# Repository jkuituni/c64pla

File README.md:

# c64pla
Implementation of the SuperPLA in the c64 'c' version in VHDL done together with Frank Buss. Note, that this version does work only as the normal SuperPLA (chip number 251715), not the one with integrated color SRAM (chip number 252535).

This is a fork from the Frank Buss' repository as that is where the original work was done. For additional information check out the webpage about this project :

https://frank-buss.de/c64/pla/index.html

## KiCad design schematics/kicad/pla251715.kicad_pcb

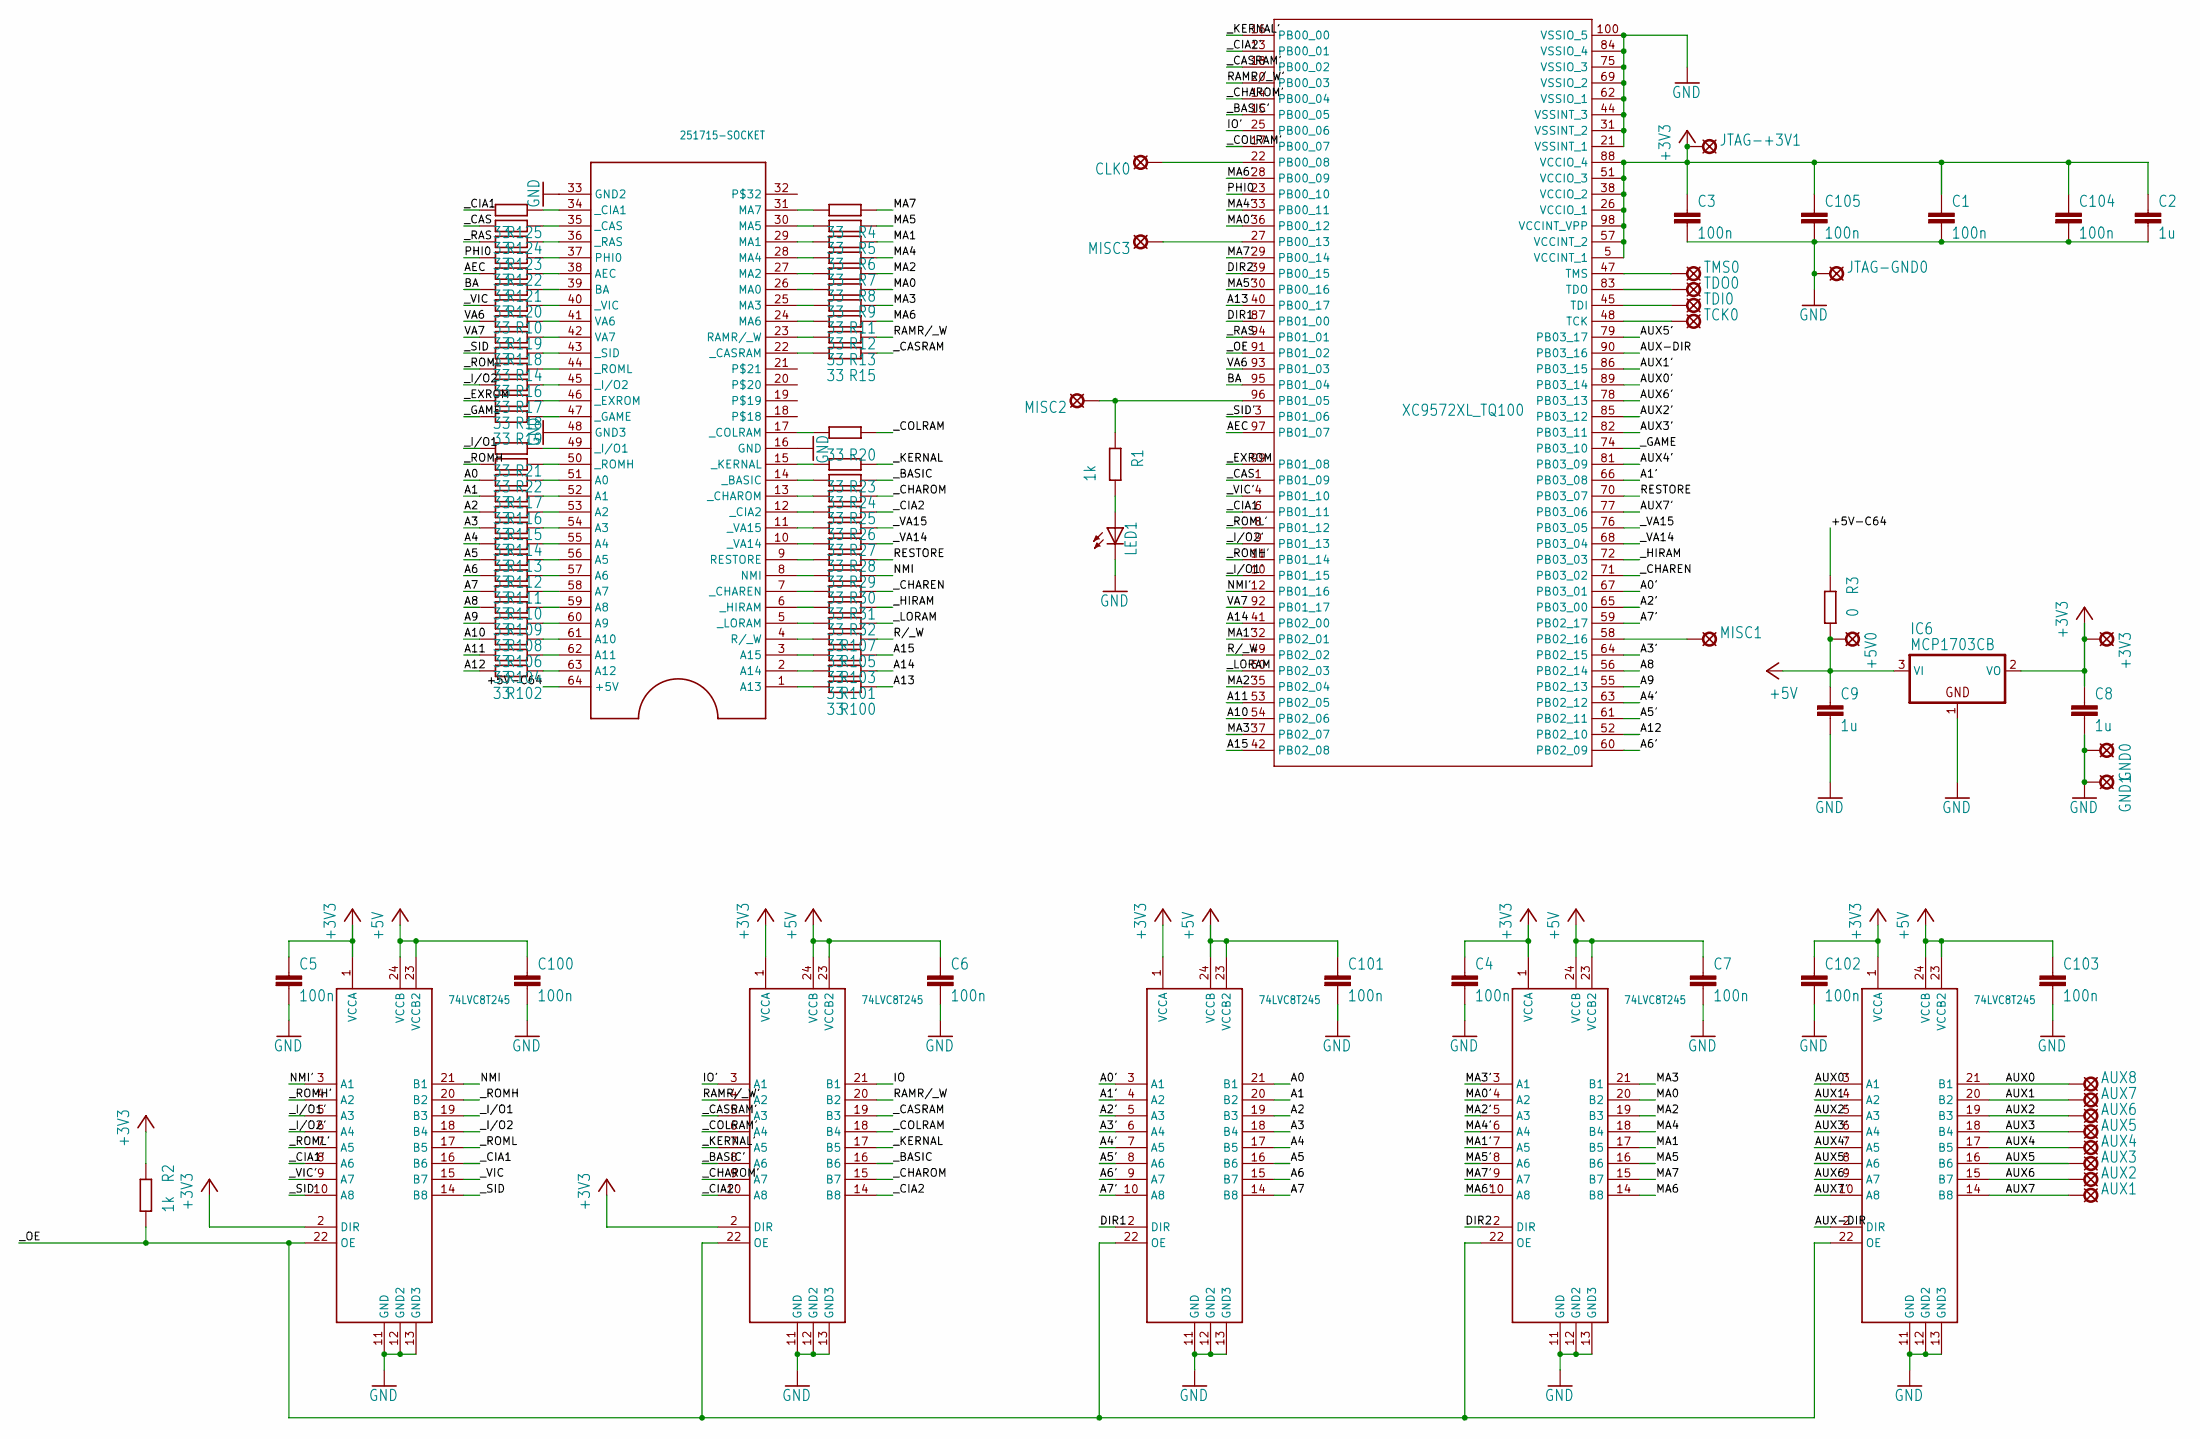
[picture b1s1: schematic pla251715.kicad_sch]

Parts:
+3V3, +5V0: LSP10
AUX1, AUX2, AUX3, AUX4, AUX5, AUX6, AUX7, AUX8: LSP10
C1, C3, C4, C5, C6, C7, C100, C101, C102, C103, C104, C105: 100n; C0603
C2, C8, C9: 1u; C1210
CLK0: LSP10
GND0, GND1: LSP10
IC1, IC3, IC4, IC5, IC100: 74LVC8T245; TSSOP24
IC2: XC9572XL_TQ100; TQ100
IC6: MCP1703CB; SOT23
JTAG-+3V1: LSP10
JTAG-GND0: LSP10
LED1: LED5MM
MISC1, MISC2, MISC3: LSP10
PLA-SOCKET0: 251715-SOCKET; 64-SPDIP
R1, R2: 1k; R0805
R3: 0; R0805
R4, R5, R6, R7, R8, R9, R10, R11, R12, R13, R14, R15, R16, R17, R18, R19, R20, R21, R22, R23, R24, R25, R26, R27, R28, R29, R30, R31, R32, R100, R101, R102, R103, R104, R105, R106, R107, R108, R109, R110, R111, R112, R113, R114, R115, R116, R117, R118, R119, R120, R121, R122, R123, R124, R125: 33; R0402
TCK0: LSP10
TDI0: LSP10
TDO0: LSP10
TMS0: LSP10

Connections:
+3V3: +3V3.MP, C1.1, C2.1, C3.1, C4.1, C5.1, C8.1, C102.1, C104.1, C105.1, IC1.1 (VCCA), IC2.5 (VCCINT_1), IC2.26 (VCCIO_1), IC2.38 (VCCIO_2), IC2.51 (VCCIO_3), IC2.57 (VCCINT_2), IC2.88 (VCCIO_4), IC2.98 (VCCINT_VPP), IC3.1 (VCCA), IC3.2 (DIR), IC4.1 (VCCA), IC4.2 (DIR), IC5.1 (VCCA), IC6.2 (VO), IC100.1 (VCCA), JTAG-+3V1.MP, R2.1
+5V: +5V0.MP, C6.1, C7.1, C9.1, C100.1, C101.1, C103.1, IC1.23 (VCCB2), IC1.24 (VCCB), IC3.23 (VCCB2), IC3.24 (VCCB), IC4.23 (VCCB2), IC4.24 (VCCB), IC5.23 (VCCB2), IC5.24 (VCCB), IC6.3 (VI), IC100.23 (VCCB2), IC100.24 (VCCB), R3.2
+5V-C64: PLA-SOCKET0.64 (+5V), R3.1
A0: IC100.21 (B1), R117.2
A0': IC2.67 (PB03_01), IC100.3 (A1)
A1: IC100.20 (B2), R116.2
A1': IC2.66 (PB03_08), IC100.4 (A2)
A2: IC100.19 (B3), R115.2
A2': IC2.65 (PB03_00), IC100.5 (A3)
A3: IC100.18 (B4), R114.2
A3': IC2.64 (PB02_15), IC100.6 (A4)
A4: IC100.17 (B5), R113.2
A4': IC2.63 (PB02_12), IC100.7 (A5)
A5: IC100.16 (B6), R112.2
A5': IC2.61 (PB02_11), IC100.8 (A6)
A6: IC100.15 (B7), R111.2
A6': IC2.60 (PB02_09), IC100.9 (A7)
A7: IC100.14 (B8), R110.2
A7': IC2.59 (PB02_17), IC100.10 (A8)
A8: IC2.56 (PB02_14), R109.2
A9: IC2.55 (PB02_13), R108.2
A10: IC2.54 (PB02_06), R106.2
A11: IC2.53 (PB02_05), R104.2
A12: IC2.52 (PB02_10), R102.2
A13: IC2.40 (PB00_17), R100.1
A14: IC2.41 (PB02_00), R101.1
A15: IC2.42 (PB02_08), R103.1
AEC: IC2.97 (PB01_07), R121.2
AUX0: AUX8.MP, IC1.21 (B1)
AUX0': IC1.3 (A1), IC2.89 (PB03_14)
AUX1: AUX7.MP, IC1.20 (B2)
AUX1': IC1.4 (A2), IC2.86 (PB03_15)
AUX2: AUX6.MP, IC1.19 (B3)
AUX2': IC1.5 (A3), IC2.85 (PB03_12)
AUX3: AUX5.MP, IC1.18 (B4)
AUX3': IC1.6 (A4), IC2.82 (PB03_11)
AUX4: AUX4.MP, IC1.17 (B5)
AUX4': IC1.7 (A5), IC2.81 (PB03_09)
AUX5: AUX3.MP, IC1.16 (B6)
AUX5': IC1.8 (A6), IC2.79 (PB03_17)
AUX6: AUX2.MP, IC1.15 (B7)
AUX6': IC1.9 (A7), IC2.78 (PB03_13)
AUX7: AUX1.MP, IC1.14 (B8)
AUX7': IC1.10 (A8), IC2.77 (PB03_06)
AUX-DIR: IC1.2 (DIR), IC2.90 (PB03_16)
BA: IC2.95 (PB01_04), R120.2
DIR1: IC2.87 (PB01_00), IC100.2 (DIR)
DIR2: IC2.39 (PB00_15), IC5.2 (DIR)
GND: C1.2, C2.2, C3.2, C4.2, C5.2, C6.2, C7.2, C8.2, C9.2, C100.2, C101.2, C102.2, C103.2, C104.2, C105.2, GND0.MP, GND1.MP, IC1.11 (GND), IC1.12 (GND2), IC1.13 (GND3), IC2.21 (VSSINT_1), IC2.31 (VSSINT_2), IC2.44 (VSSINT_3), IC2.62 (VSSIO_1), IC2.69 (VSSIO_2), IC2.75 (VSSIO_3), IC2.84 (VSSIO_4), IC2.100 (VSSIO_5), IC3.11 (GND), IC3.12 (GND2), IC3.13 (GND3), IC4.11 (GND), IC4.12 (GND2), IC4.13 (GND3), IC5.11 (GND), IC5.12 (GND2), IC5.13 (GND3), IC6.1 (GND), IC100.11 (GND), IC100.12 (GND2), IC100.13 (GND3), JTAG-GND0.MP, LED1.K (C), PLA-SOCKET0.16 (GND), PLA-SOCKET0.33 (GND2), PLA-SOCKET0.48 (GND3)
IO: IC4.21 (B1)
IO': IC2.25 (PB00_06), IC4.3 (A1)
MA0: IC5.20 (B2), R9.1
MA0': IC2.36 (PB00_12), IC5.4 (A2)
MA1: IC5.17 (B5), R6.1
MA1': IC2.32 (PB02_01), IC5.7 (A5)
MA2: IC5.19 (B3), R8.1
MA2': IC2.35 (PB02_04), IC5.5 (A3)
MA3: IC5.21 (B1), R11.1
MA3': IC2.37 (PB02_07), IC5.3 (A1)
MA4: IC5.18 (B4), R7.1
MA4': IC2.33 (PB00_11), IC5.6 (A4)
MA5: IC5.16 (B6), R5.1
MA5': IC2.30 (PB00_16), IC5.8 (A6)
MA6: IC5.14 (B8), R12.1
MA6': IC2.28 (PB00_09), IC5.10 (A8)
MA7: IC5.15 (B7), R4.1
MA7': IC2.29 (PB00_14), IC5.9 (A7)
unnamed: IC2.96 (PB01_05), MISC2.MP, R1.1
unnamed: IC2.58 (PB02_16), MISC1.MP
unnamed: IC2.27 (PB00_13), MISC3.MP
unnamed: LED1.A, R1.2
unnamed: CLK0.MP, IC2.22 (PB00_08)
unnamed: PLA-SOCKET0.17 (_COLRAM), R20.2
unnamed: PLA-SOCKET0.31 (MA7), R4.2
unnamed: PLA-SOCKET0.30 (MA5), R5.2
unnamed: PLA-SOCKET0.15 (_KERNAL), R23.2
unnamed: PLA-SOCKET0.29 (MA1), R6.2
unnamed: PLA-SOCKET0.28 (MA4), R7.2
unnamed: PLA-SOCKET0.27 (MA2), R8.2
unnamed: PLA-SOCKET0.26 (MA0), R9.2
unnamed: PLA-SOCKET0.25 (MA3), R11.2
unnamed: PLA-SOCKET0.24 (MA6), R12.2
unnamed: PLA-SOCKET0.23 (RAMR/_W), R13.2
unnamed: PLA-SOCKET0.22 (_CASRAM), R15.2
unnamed: PLA-SOCKET0.14 (_BASIC), R24.2
unnamed: PLA-SOCKET0.13 (_CHAROM), R25.2
unnamed: PLA-SOCKET0.12 (_CIA2), R26.2
unnamed: PLA-SOCKET0.11 (_VA15), R27.2
unnamed: PLA-SOCKET0.10 (_VA14), R28.2
unnamed: PLA-SOCKET0.9 (RESTORE), R29.2
unnamed: PLA-SOCKET0.8 (NMI), R30.2
unnamed: PLA-SOCKET0.7 (_CHAREN), R31.2
unnamed: PLA-SOCKET0.6 (_HIRAM), R32.2
unnamed: PLA-SOCKET0.5 (_LORAM), R107.2
unnamed: PLA-SOCKET0.4 (R/_W), R105.2
unnamed: PLA-SOCKET0.3 (A15), R103.2
unnamed: PLA-SOCKET0.2 (A14), R101.2
unnamed: PLA-SOCKET0.1 (A13), R100.2
unnamed: PLA-SOCKET0.63 (A12), R102.1
unnamed: PLA-SOCKET0.62 (A11), R104.1
unnamed: PLA-SOCKET0.61 (A10), R106.1
unnamed: PLA-SOCKET0.60 (A9), R108.1
unnamed: PLA-SOCKET0.59 (A8), R109.1
unnamed: PLA-SOCKET0.58 (A7), R110.1
unnamed: PLA-SOCKET0.57 (A6), R111.1
unnamed: PLA-SOCKET0.56 (A5), R112.1
unnamed: PLA-SOCKET0.55 (A4), R113.1
unnamed: PLA-SOCKET0.54 (A3), R114.1
unnamed: PLA-SOCKET0.53 (A2), R115.1
unnamed: PLA-SOCKET0.52 (A1), R116.1
unnamed: PLA-SOCKET0.51 (A0), R117.1
unnamed: PLA-SOCKET0.50 (_ROMH), R22.1
unnamed: PLA-SOCKET0.49 (_I/O1), R21.1
unnamed: PLA-SOCKET0.47 (_GAME), R19.1
unnamed: PLA-SOCKET0.46 (_EXROM), R18.1
unnamed: PLA-SOCKET0.45 (_I/O2), R17.1
unnamed: PLA-SOCKET0.44 (_ROML), R16.1
unnamed: PLA-SOCKET0.43 (_SID), R14.1
unnamed: PLA-SOCKET0.42 (VA7), R118.1
unnamed: PLA-SOCKET0.41 (VA6), R119.1
unnamed: PLA-SOCKET0.40 (_VIC), R10.1
unnamed: PLA-SOCKET0.39 (BA), R120.1
unnamed: PLA-SOCKET0.38 (AEC), R121.1
unnamed: PLA-SOCKET0.37 (PHI0), R122.1
unnamed: PLA-SOCKET0.36 (_RAS), R123.1
unnamed: PLA-SOCKET0.35 (_CAS), R124.1
unnamed: PLA-SOCKET0.34 (_CIA1), R125.1
NMI: IC3.21 (B1), R30.1
NMI': IC2.12 (PB01_16), IC3.3 (A1)
PHI0: IC2.23 (PB00_10), R122.2
R/_W: IC2.49 (PB02_02), R105.1
RAMR/_W: IC4.20 (B2), R13.1
RAMR/_W': IC2.20 (PB00_03), IC4.4 (A2)
RESTORE: IC2.70 (PB03_07), R29.1
TCK: IC2.48 (TCK), TCK0.MP
TDI: IC2.45 (TDI), TDI0.MP
TDO: IC2.83 (TDO), TDO0.MP
TMS: IC2.47 (TMS), TMS0.MP
VA6: IC2.93 (PB01_03), R119.2
VA7: IC2.92 (PB01_17), R118.2
_BASIC: IC4.16 (B6), R24.1
_BASIC': IC2.15 (PB00_05), IC4.8 (A6)
_CAS: IC2.1 (PB01_09), R124.2
_CASRAM: IC4.19 (B3), R15.1
_CASRAM': IC2.18 (PB00_02), IC4.5 (A3)
_CHAREN: IC2.71 (PB03_02), R31.1
_CHAROM: IC4.15 (B7), R25.1
_CHAROM': IC2.14 (PB00_04), IC4.9 (A7)
_CIA1: IC3.16 (B6), R125.2
_CIA1': IC2.6 (PB01_11), IC3.8 (A6)
_CIA2: IC4.14 (B8), R26.1
_CIA2': IC2.13 (PB00_01), IC4.10 (A8)
_COLRAM: IC4.18 (B4), R20.1
_COLRAM': IC2.17 (PB00_07), IC4.6 (A4)
_EXROM: IC2.99 (PB01_08), R18.2
_GAME: IC2.74 (PB03_10), R19.2
_HIRAM: IC2.72 (PB03_03), R32.1
_I/O1: IC3.19 (B3), R21.2
_I/O1': IC2.10 (PB01_15), IC3.5 (A3)
_I/O2: IC3.18 (B4), R17.2
_I/O2': IC2.9 (PB01_13), IC3.6 (A4)
_KERNAL: IC4.17 (B5), R23.1
_KERNAL': IC2.16 (PB00_00), IC4.7 (A5)
_LORAM: IC2.50 (PB02_03), R107.1
_OE: IC1.22 (OE), IC2.91 (PB01_02), IC3.22 (OE), IC4.22 (OE), IC5.22 (OE), IC100.22 (OE), R2.2
_RAS: IC2.94 (PB01_01), R123.2
_ROMH: IC3.20 (B2), R22.2
_ROMH': IC2.11 (PB01_14), IC3.4 (A2)
_ROML: IC3.17 (B5), R16.2
_ROML': IC2.8 (PB01_12), IC3.7 (A5)
_SID: IC3.14 (B8), R14.2
_SID': IC2.3 (PB01_06), IC3.10 (A8)
_VA14: IC2.68 (PB03_04), R28.1
_VA15: IC2.76 (PB03_05), R27.1
_VIC: IC3.15 (B7), R10.2
_VIC': IC2.4 (PB01_10), IC3.9 (A7)

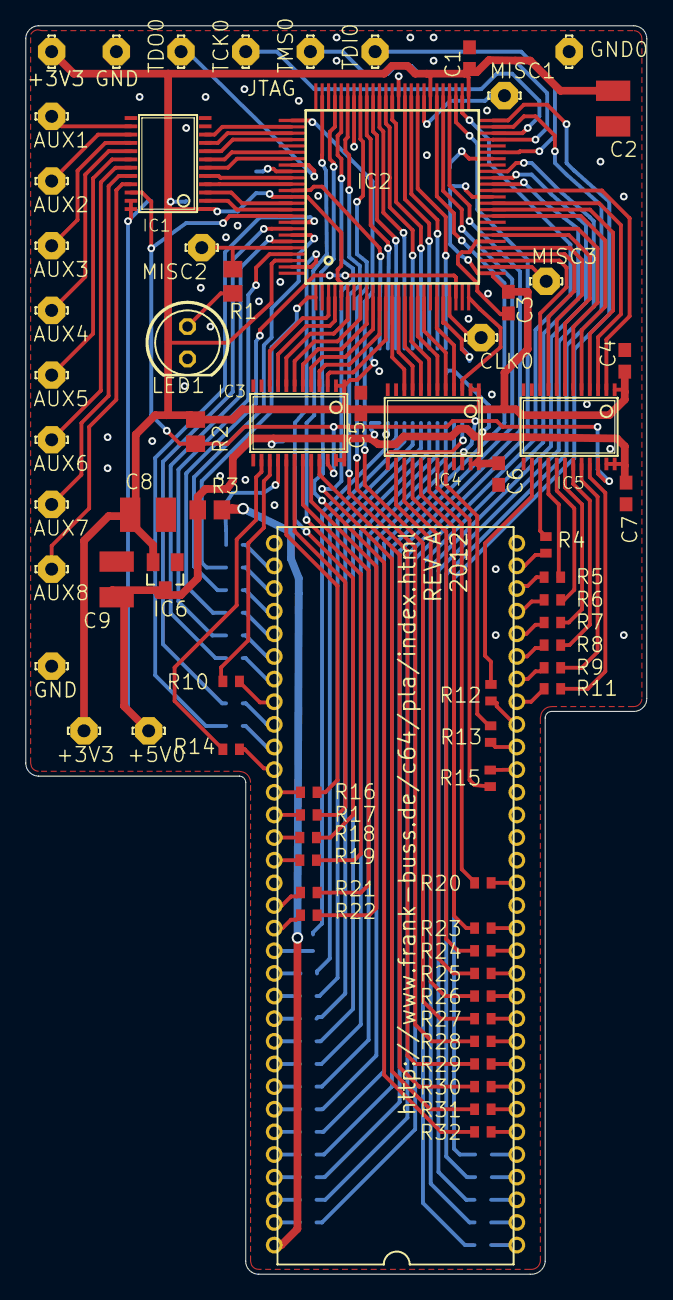
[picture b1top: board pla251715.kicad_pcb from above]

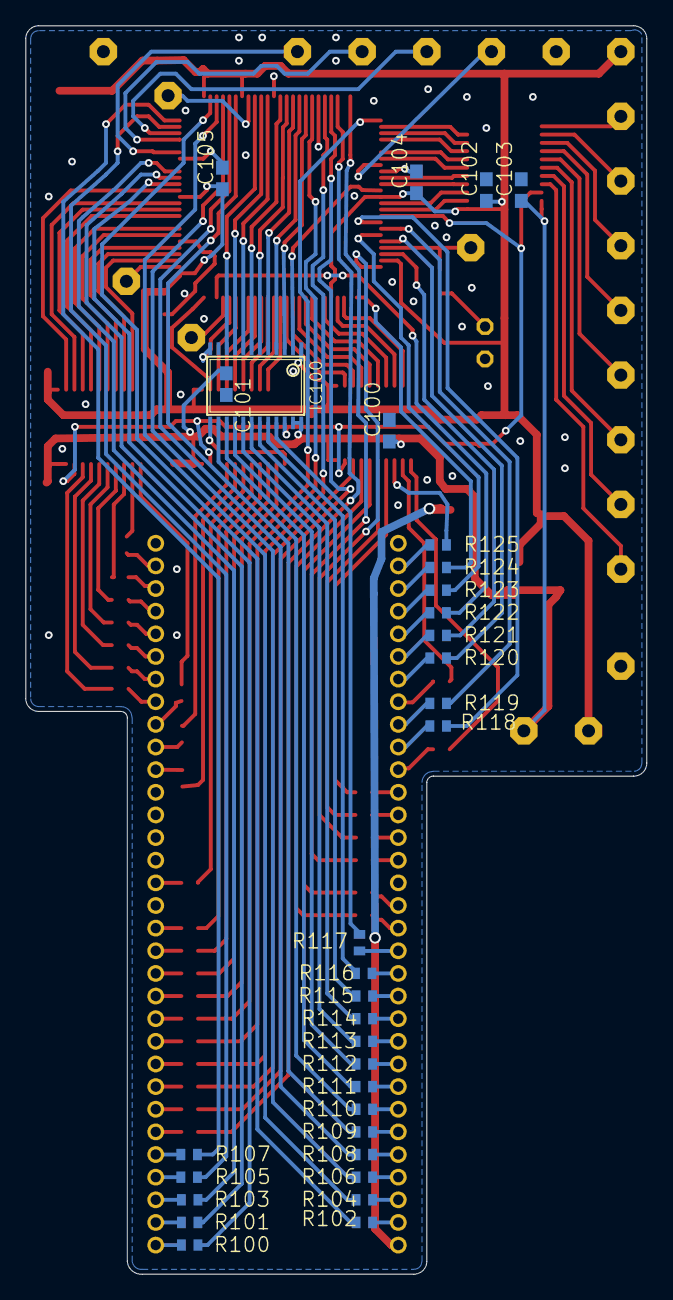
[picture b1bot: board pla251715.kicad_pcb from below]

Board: 2 copper layers, 48.8 x 98.0 mm, 104 parts (33 on the bottom side), 175 nets.

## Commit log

2023-10-23 Changed README to reflect the state of this repository.
2023-10-23 Elaborated the SuperPLA part numbers on the README.
2025-02-04 Re-structured schematics. Added KiCAD conversion.
2025-02-07 Typo fix on README.
